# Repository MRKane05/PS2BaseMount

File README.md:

This is a dump of the KiCad project for the Junkstation PS2 project I made a few years ago. I'm really just backing it up for prosperity. 
I'm taking no responsibility for this and it really should be used only as reference.

It's worth noting that there are a couple of mistakes on the board that I haven't fixed:
-The Ethernet wiring for the Mango isn't correct, and troubleshooting it was exceedingly difficult, so much so that I didn't write it down when I got it right, I just put the lid on it
-The Ethernet lines for the Mango shouldn't be pulled down to Ground but pulled to the "R0" pin on the Mango. This allows a successful ethernet connection
-The SD Card slot wired up for game loading through the memory card port is correctly wired

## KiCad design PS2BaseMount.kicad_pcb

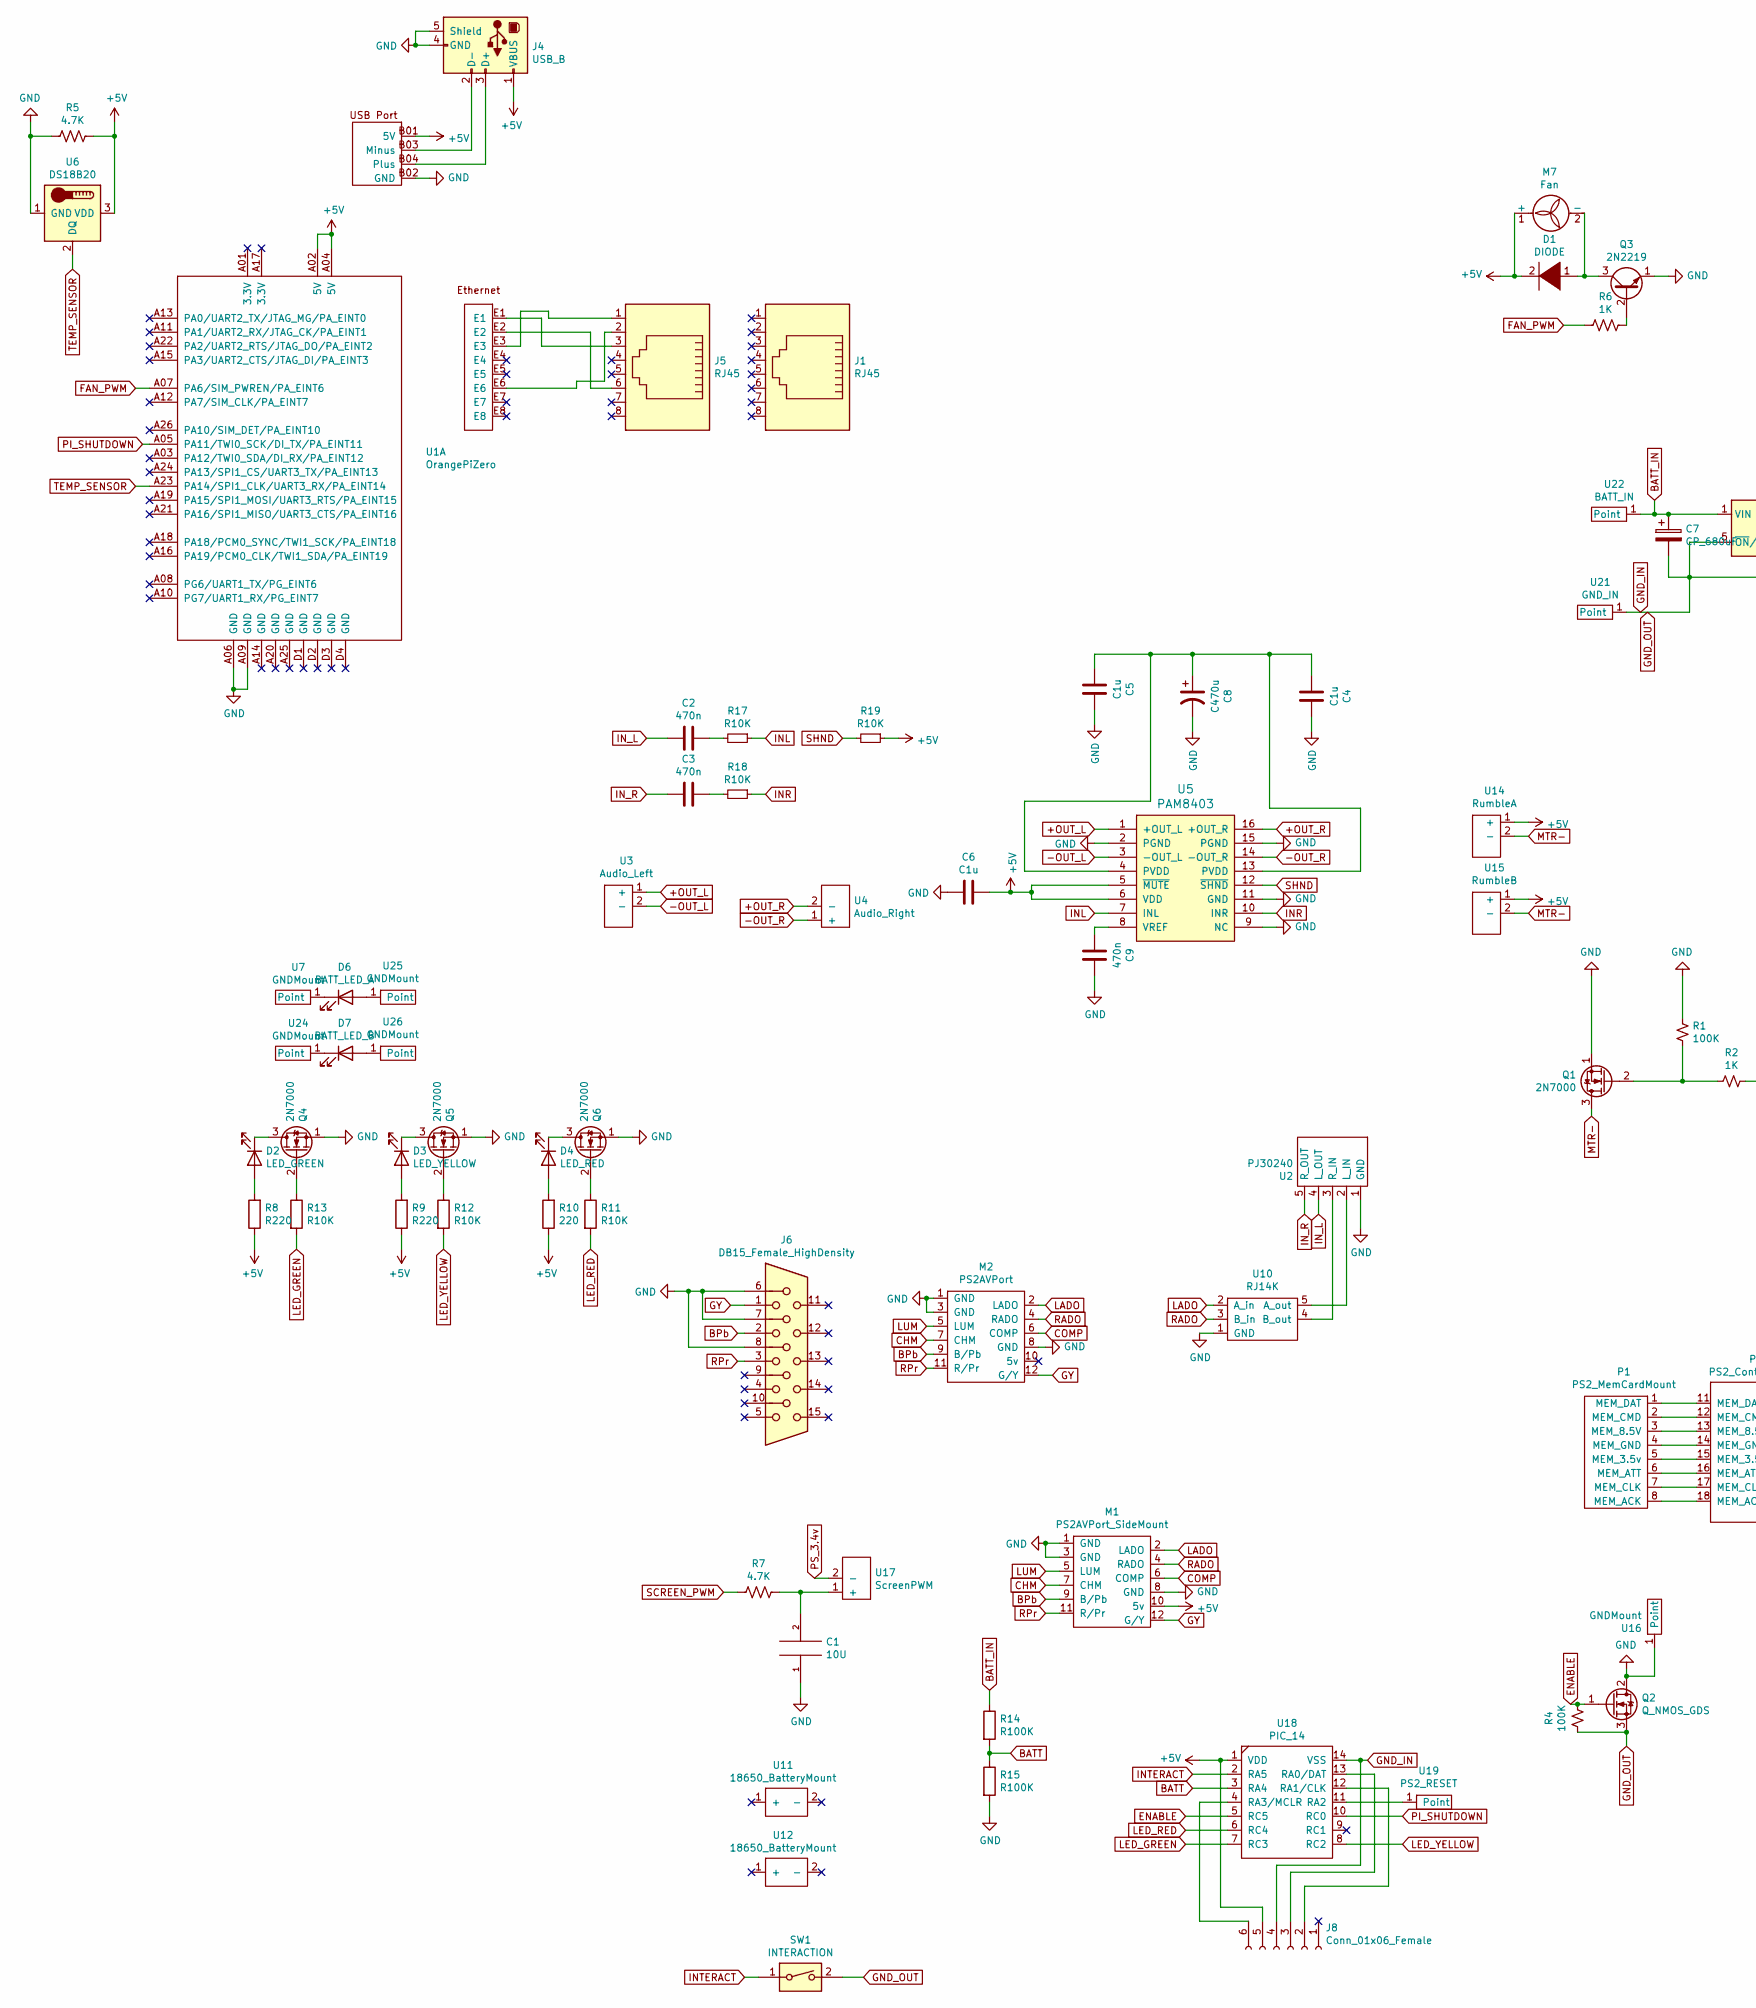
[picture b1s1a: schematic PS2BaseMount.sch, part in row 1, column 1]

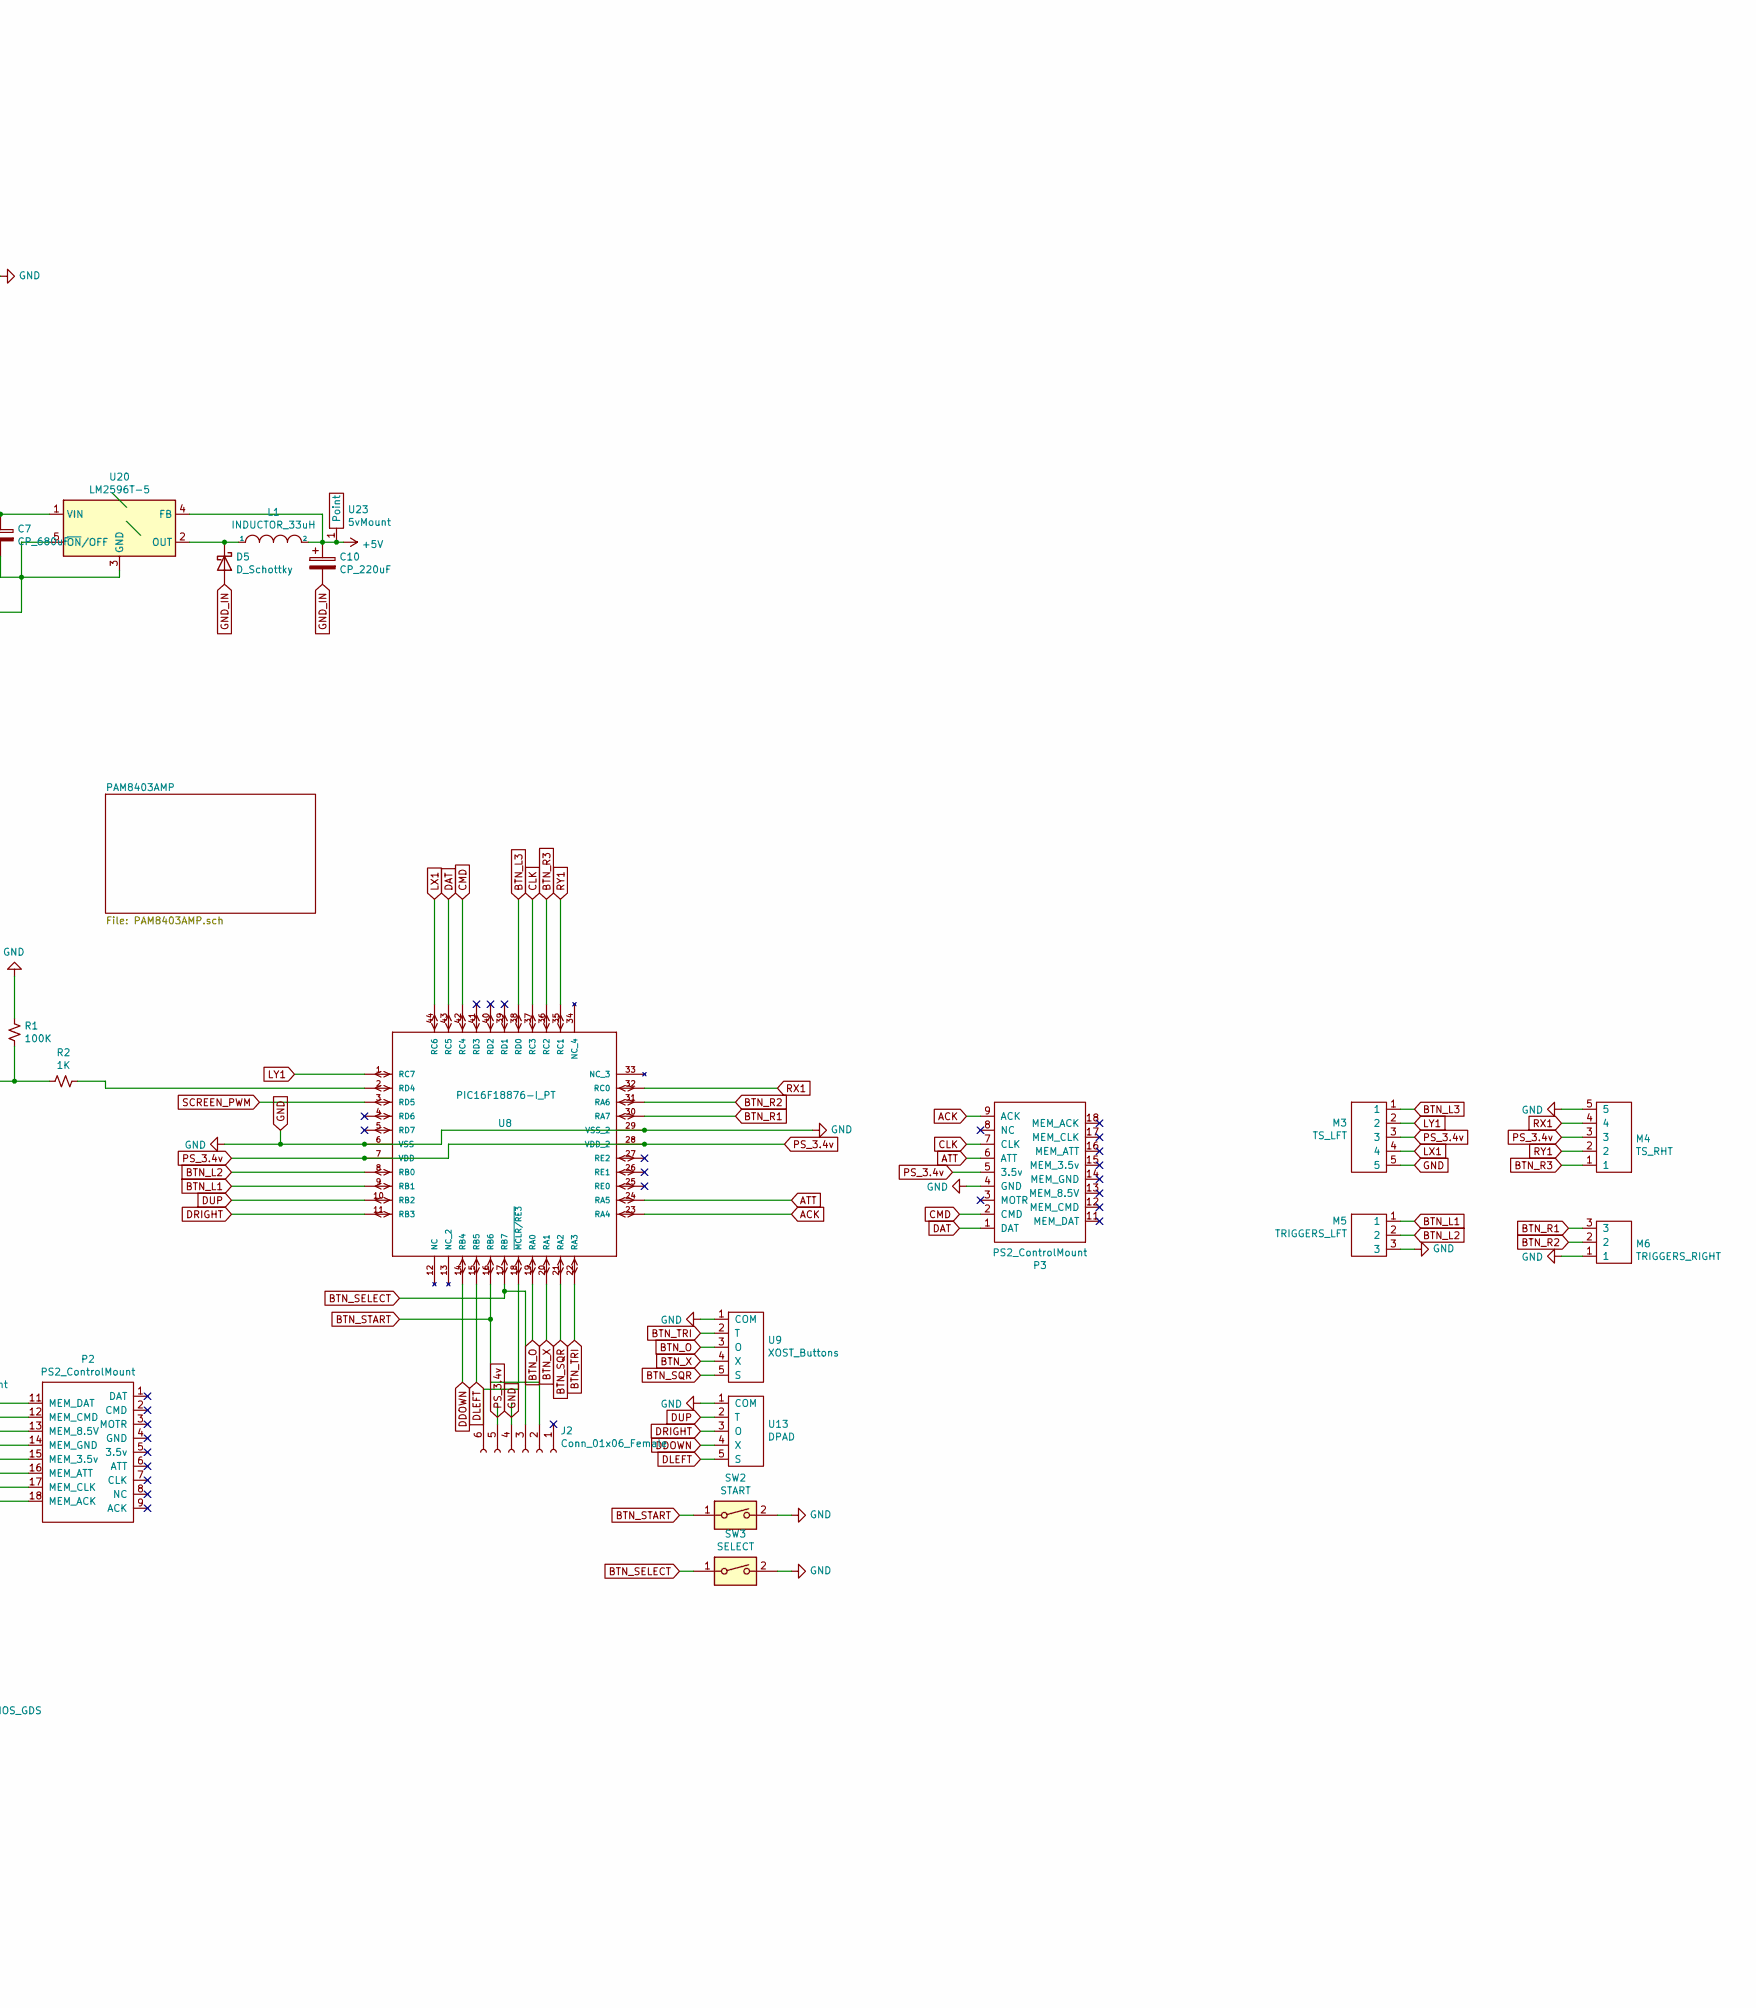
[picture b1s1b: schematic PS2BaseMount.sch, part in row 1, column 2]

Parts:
C1: 10U; C_1206_3216Metric_Pad1.42x1.75mm_HandSolder
C2, C3, C9: 470n; C_1206_3216Metric_Pad1.42x1.75mm_HandSolder; LCSC C1871
C4, C5, C6: C1u; C_1206_3216Metric_Pad1.42x1.75mm_HandSolder; LCSC C1848
C7: CP_680uF; CP_Radial_D8.0mm_P2.50mm
C8: C470u; CP_Radial_D8.0mm_P2.50mm
C10: CP_220uF; CP_Radial_D8.0mm_P3.50mm
D1: DIODE; Crystal_SMD_5032-2Pin_5.0x3.2mm_HandSoldering
D2: LED_GREEN; LED_D3.0mm
D3: LED_YELLOW; LED_D3.0mm
D4: LED_RED; LED_D3.0mm
D5: D_Schottky; Crystal_SMD_5032-2Pin_5.0x3.2mm_HandSoldering; LCSC C8678
D6: BATT_LED_A; LED_D3.0mm
D7: BATT_LED_B; LED_D3.0mm
J1, J5: RJ45; RJ45_Floating
J2, J8: Conn_01x06_Female; PinHeader_1x06_P2.54mm_Horizontal
J4: USB_B; USB_A_Custom_Throughhole_MountGuide
J6: DB15_Female_HighDensity; ScreenBoardArea
L1: INDUCTOR_33uH; L_12x12mm_H8mm; LCSC C169375
M1: PS2AVPort_SideMount; PS2_AVPort_Complete_MountSilk
M2: PS2AVPort; PS2_AVPort_Complete
M3: TS_LFT; JST_1.25_5Pin
M4: TS_RHT; JST_1.25_5Pin
M5: TRIGGERS_LFT; JST_1.25_3Pin
M6: TRIGGERS_RIGHT; JST_1.25_3Pin
M7: Fan; JST_1.5_2Pin
P1: PS2_MemCardMount; PS2_MemCardMountPoints
P2, P3: PS2_ControlMount; PS2_BoardMountFootprint
Q1, Q4, Q5, Q6: 2N7000; 2N7000_HandSolder
Q2: Q_NMOS_GDS; TO-220F-3_Vertical
Q3: 2N2219; 2N7000_HandSolder
R1, R4: 100K; R_1206_3216Metric_Pad1.42x1.75mm_HandSolder
R2, R6: 1K; R_1206_3216Metric_Pad1.42x1.75mm_HandSolder
R5: 4.7K; R_2010_5025Metric_Pad1.52x2.65mm_HandSolder
R7: 4.7K; D_2010_5025Metric_Pad1.52x2.65mm_HandSolder
R8, R9: R220; R_1206_3216Metric_Pad1.42x1.75mm_HandSolder
R10: 220; R_1206_3216Metric_Pad1.42x1.75mm_HandSolder
R11, R12, R13: R10K; R_1206_3216Metric_Pad1.42x1.75mm_HandSolder
R14, R15: R100K; R_1206_3216Metric_Pad1.42x1.75mm_HandSolder
R17, R18, R19: R10K; R_1206_3216Metric_Pad1.42x1.75mm_HandSolder; LCSC C17902
SW1: INTERACTION; SMT_2X4X3.5MM
SW2: START; SquishyTact
SW3: SELECT; SquishyTact
U1: OrangePiZero
U2: PJ30240; AudioJack_PJ30240
U3: Audio_Left; JST_1.5_2Pin
U4: Audio_Right; JST_1.5_2Pin
U5: PAM8403; so-16; LCSC C348830
U6: DS18B20; TO-92_Inline
U7, U16, U24, U25, U26: GNDMount; GND
U8: PIC16F18876-I_PT
U9: XOST_Buttons; XOST_ButtonsV2
U10: RJ14K; RJ14K_Modified
U11, U12: 18650_BatteryMount; 18650_3xHolderV3
U13: DPAD; DPad_Buttons
U14: RumbleA; JST_1.5_2Pin
U15: RumbleB; JST_1.5_2Pin
U17: ScreenPWM; JST_1.5_2Pin
U18: PIC_14; DIP-14_W7.62mm_LongPads
U19: PS2_RESET; GND
U20: LM2596T-5; TO-263-5_TabPin3; LCSC C10002
U21: GND_IN; MountPoint
U22: BATT_IN; MountPoint
U23: 5vMount; MountPoint

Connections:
+5V: C6.1, C10.1, D1.2 (A), J4.1 (VBUS), J8.5, L1.2, M1.10 (5v), M7.1 (+), R5.1, R8.1, R9.1, R10.1, R19.1, U1.A02 (5V), U1.A04 (5V), U1.B01 (5V), U5.5 (~MUTE), U5.6 (VDD), U6.3 (VDD), U14.1 (+), U15.1 (+), U18.1 (VDD), U20.4 (FB), U23.1
+OUT_L: U3.1 (+), U5.1 (+OUT_L)
+OUT_R: U4.2 (-), U5.16 (+OUT_R)
-OUT_L: U3.2 (-), U5.3 (-OUT_L)
-OUT_R: U4.1 (+), U5.14 (-OUT_R)
ACK: P3.9 (ACK), U8.23 (RA4)
ATT: P3.6 (ATT), U8.24 (RA5)
BATT: R14.2, R15.1, U18.3 (RA4)
BATT_IN: C7.1, R14.1, U20.1 (VIN), U22.1
BPb: J6.2, M1.9 (B/Pb), M2.9 (B/Pb)
BTN_L1: M5.1, U8.9 (RB1)
BTN_L2: M5.2, U8.8 (RB0)
BTN_L3: M3.1, U8.38 (RD0)
BTN_O: U8.19 (RA0), U9.3 (O)
BTN_R1: M6.3, U8.30 (RA7)
BTN_R2: M6.2, U8.31 (RA6)
BTN_R3: M4.1, U8.36 (RC2)
BTN_SELECT: J2.3, SW3.1, U8.17 (RB7)
BTN_SQR: U8.21 (RA2), U9.5 (S)
BTN_START: J2.2, SW2.1, U8.16 (RB6)
BTN_TRI: U8.22 (RA3), U9.2 (T)
BTN_X: U8.20 (RA1), U9.4 (X)
CHM: M1.7 (CHM), M2.7 (CHM)
CLK: P3.7 (CLK), U8.37 (RC3)
CMD: P3.2 (CMD), U8.42 (RC4)
COMP: M1.6 (COMP), M2.6 (COMP)
DAT: P3.1 (DAT), U8.43 (RC5)
DDOWN: U8.14 (RB4), U13.4 (X)
DLEFT: U8.15 (RB5), U13.5 (S)
DRIGHT: U8.11 (RB3), U13.3 (O)
DUP: U8.10 (RB2), U13.2 (T)
ENABLE: Q2.1 (G), R4.1, U18.5 (RC5)
FAN_PWM: R6.2, U1.A07 (PA6/SIM_PWREN/PA_EINT6)
GND: C1.1, C4.1, C5.1, C6.2, C8.2, C9.1, J2.4, J4.4 (GND), J4.5 (Shield), J6.6, J6.7, J6.8, M1.1 (GND), M1.3 (GND), M1.8 (GND), M2.1 (GND), M2.3 (GND), M2.8 (GND), M3.5, M4.5, M5.3, M6.1, P3.4 (GND), Q1.1 (S), Q2.2 (D), Q3.1 (E), Q4.1 (S), Q5.1 (S), Q6.1 (S), R1.1, R5.2, R15.2, SW2.2, SW3.2, U1.A06 (GND), U1.A09 (GND), U1.B02 (GND), U2.1 (GND), U5.2 (PGND), U5.9 (NC), U5.11 (GND), U5.15 (PGND), U6.1 (GND), U8.6 (VSS), U8.29 (VSS_2), U9.1 (COM), U10.1 (GND), U13.1 (COM), U16.1
GND_IN: C7.2, C10.2, D5.2 (A), J8.4, Q2.3 (S), R4.2, SW1.2, U18.14 (VSS), U20.3 (GND), U20.5 (~ON~/OFF), U21.1
GY: J6.1, M1.12 (G/Y), M2.12 (G/Y)
INL: R17.1, U5.7 (INL)
INR: R18.1, U5.10 (INR)
INTERACT: SW1.1, U18.2 (RA5)
IN_L: C2.2, U2.4 (L_OUT)
IN_R: C3.2, U2.5 (R_OUT)
LADO: M1.2 (LADO), M2.2 (LADO), U10.2 (A_in)
LED_GREEN: R13.2, U18.7 (RC3)
LED_RED: R11.2, U18.6 (RC4)
LED_YELLOW: R12.2, U18.8 (RC2)
LUM: M1.5 (LUM), M2.5 (LUM)
LX1: M3.4, U8.44 (RC6)
LY1: M3.2, U8.1 (RC7)
MTR-: Q1.3 (D), U14.2 (-), U15.2 (-)
unnamed: C1.2, R7.1, U17.1 (+)
unnamed: C2.1, R17.2
unnamed: C3.1, R18.2
unnamed: C4.2, C5.2, C8.1, U5.4 (PVDD), U5.13 (PVDD)
unnamed: C9.2, U5.8 (VREF)
unnamed: D1.1 (K), M7.2 (-), Q3.3 (C)
unnamed: D2.1 (K), Q4.3 (D)
unnamed: D2.2 (A), R8.2
unnamed: D3.1 (K), Q5.3 (D)
unnamed: D3.2 (A), R9.2
unnamed: D4.1 (K), Q6.3 (D)
unnamed: D4.2 (A), R10.2
unnamed: D5.1 (K), L1.1, U20.2 (OUT)
unnamed: D6.1 (K), U7.1
unnamed: D6.2 (A), U25.1
unnamed: D7.1 (K), U24.1
unnamed: D7.2 (A), U26.1
unnamed: J2.6, U8.18 (~MCLR/RE3)
unnamed: J4.2 (D-), U1.B03 (Minus)
unnamed: J4.3 (D+), U1.B04 (Plus)
unnamed: J5.1, U1.E3
unnamed: J5.2, U1.E6
unnamed: J5.3, U1.E1
unnamed: J5.6, U1.E2
unnamed: J8.2, U18.12 (RA1/CLK)
unnamed: J8.3, U18.13 (RA0/DAT)
unnamed: J8.6, U18.4 (RA3/MCLR)
unnamed: P1.1 (MEM_DAT), P2.11 (MEM_DAT)
unnamed: P1.2 (MEM_CMD), P2.12 (MEM_CMD)
unnamed: P1.3 (MEM_8.5V), P2.13 (MEM_8.5V)
unnamed: P1.4 (MEM_GND), P2.14 (MEM_GND)
unnamed: P1.5 (MEM_3.5v), P2.15 (MEM_3.5v)
unnamed: P1.6 (MEM_ATT), P2.16 (MEM_ATT)
unnamed: P1.7 (MEM_CLK), P2.17 (MEM_CLK)
unnamed: P1.8 (MEM_ACK), P2.18 (MEM_ACK)
unnamed: Q1.2 (G), R1.2, R2.2
unnamed: Q3.2 (B), R6.1
unnamed: Q4.2 (G), R13.1
unnamed: Q5.2 (G), R12.1
unnamed: Q6.2 (G), R11.1
unnamed: R2.1, U8.2 (RD4)
unnamed: U2.3 (R_IN), U10.4 (B_out)
unnamed: U2.2 (L_IN), U10.5 (A_out)
unnamed: U18.11 (RA2), U19.1
PI_SHUTDOWN: U1.A05 (PA11/TWI0_SCK/DI_TX/PA_EINT11), U18.10 (RC0)
PS_3.4v: J2.5, M3.3, M4.3, P3.5 (3.5v), U8.7 (VDD), U8.28 (VDD_2), U17.2 (-)
RADO: M1.4 (RADO), M2.4 (RADO), U10.3 (B_in)
RPr: J6.3, M1.11 (R/Pr), M2.11 (R/Pr)
RX1: M4.4, U8.32 (RC0)
RY1: M4.2, U8.35 (RC1)
SCREEN_PWM: R7.2, U8.3 (RD5)
SHND: R19.2, U5.12 (~SHND)
TEMP_SENSOR: U1.A23 (PA14/SPI1_CLK/UART3_RX/PA_EINT14), U6.2 (DQ)

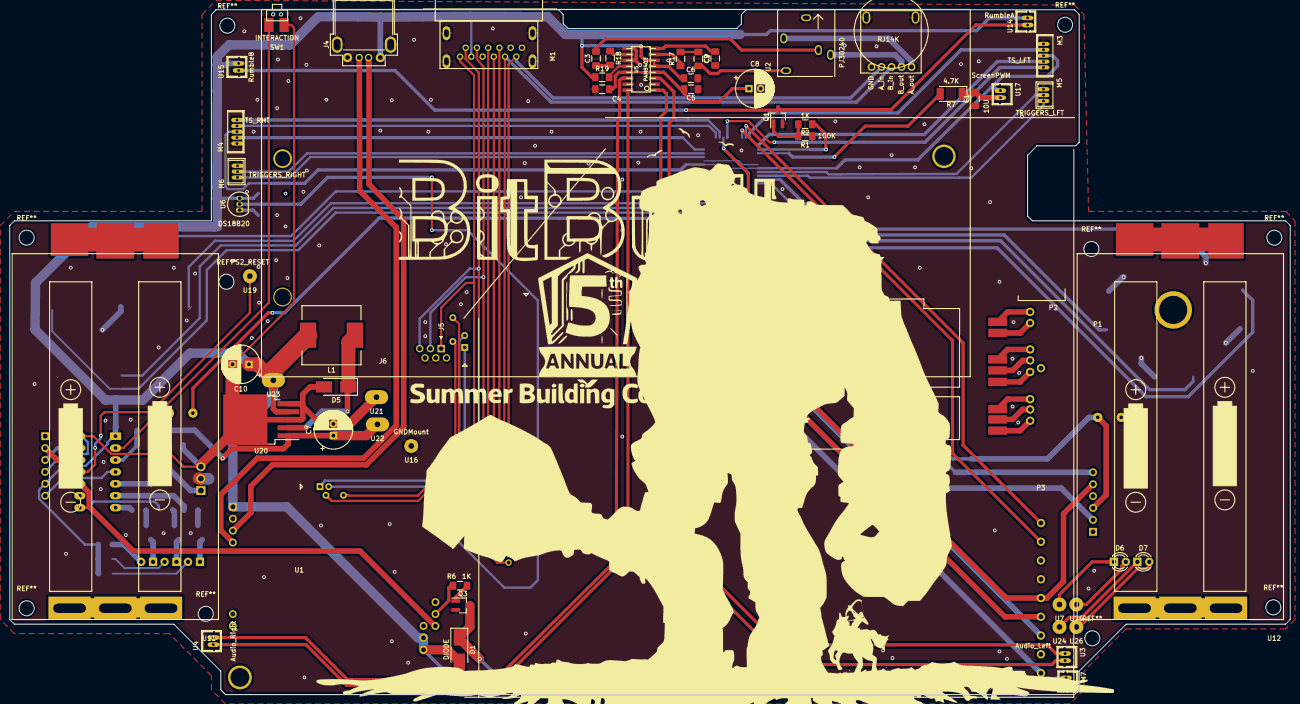
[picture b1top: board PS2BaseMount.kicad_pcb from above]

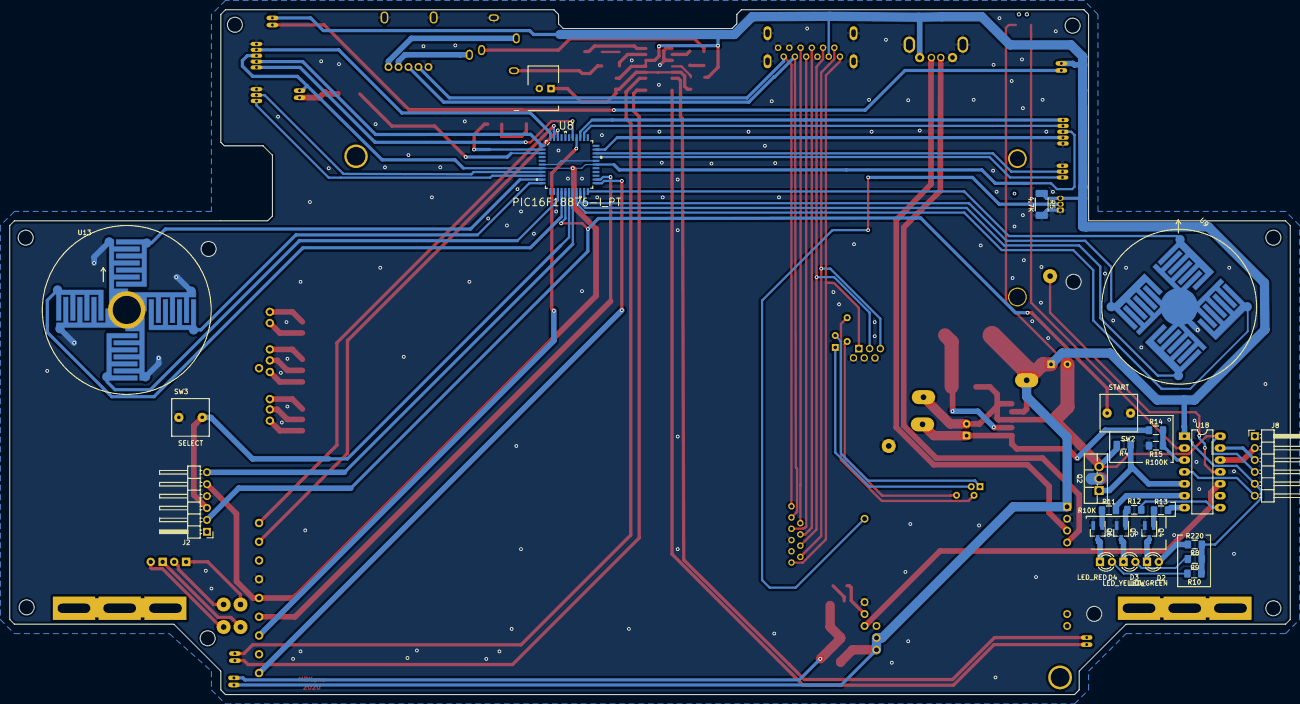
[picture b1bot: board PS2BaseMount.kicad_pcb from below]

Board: 2 copper layers, 273.0 x 146.0 mm, 86 parts (25 on the bottom side), 102 nets.

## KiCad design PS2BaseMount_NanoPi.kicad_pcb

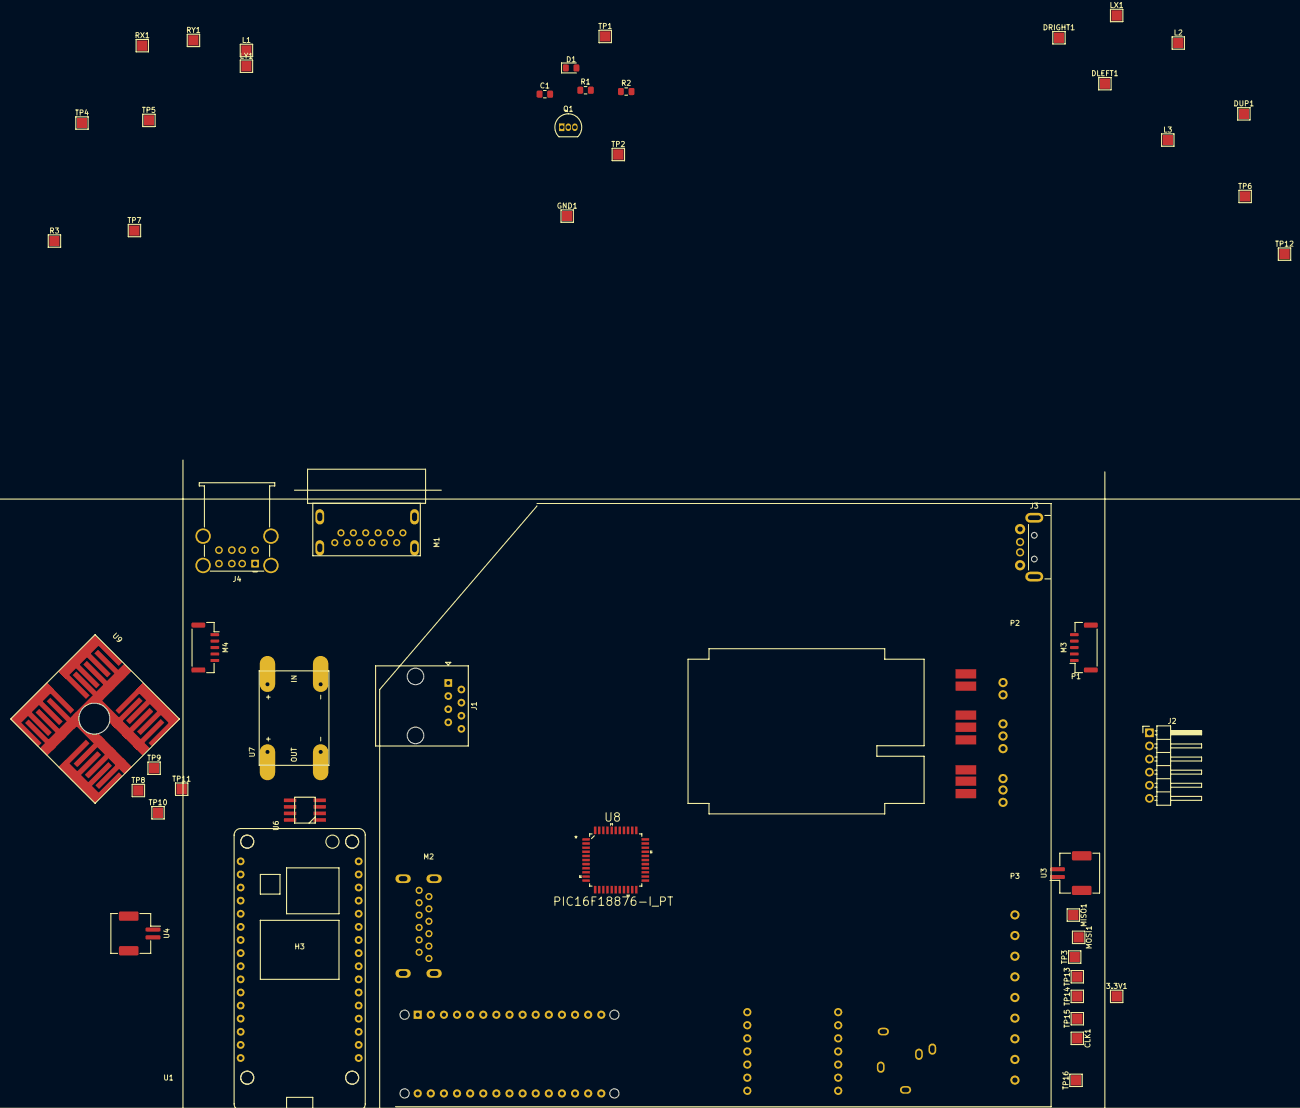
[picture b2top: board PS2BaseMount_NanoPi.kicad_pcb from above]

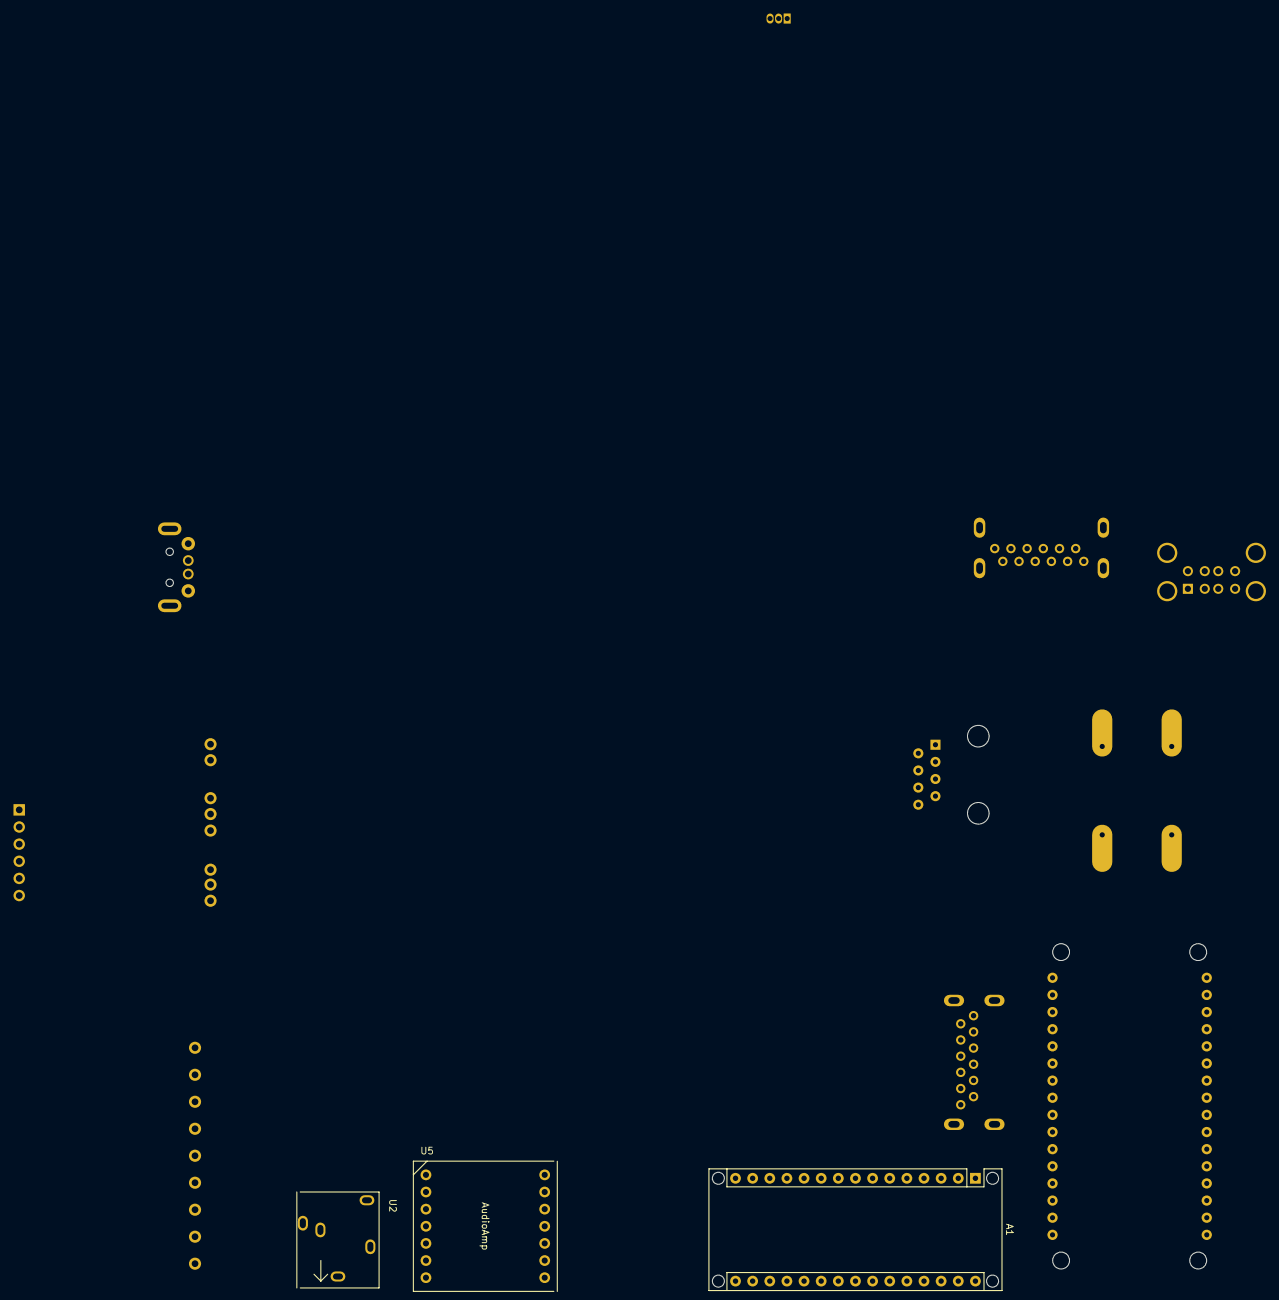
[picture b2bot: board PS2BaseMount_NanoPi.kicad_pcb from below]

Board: 2 copper layers, 58 parts (3 on the bottom side), 46 nets, no tracks yet.

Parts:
3.3V1: TP6; TestPoint_Pad_2.0x2.0mm
A1: Arduino_Nano_v3.x; Arduino_Nano_WithMountingHoles
C1: 10uF; C_0805_2012Metric_Pad1.15x1.40mm_HandSolder
CLK1: TP19; TestPoint_Pad_2.0x2.0mm
D1: 1N58XX; D_0805_2012Metric_Pad1.15x1.40mm_HandSolder
DLEFT1: TP7; TestPoint_Pad_2.0x2.0mm
DRIGHT1: TP8; TestPoint_Pad_2.0x2.0mm
DUP1: TP27; TestPoint_Pad_2.0x2.0mm
GND1: TP5; TestPoint_Pad_2.0x2.0mm
J1: RJ45; RJ45_Amphenol_54602-x08_Horizontal
J2: Conn_01x06_Female; PinHeader_1x06_P2.54mm_Horizontal
J3: USB_B; USB_A_Custom_Throughhole
J4: USB_A_Dual; USB_A_Wuerth_61400826021_Horizontal_Stacked
L1: TP9; TestPoint_Pad_2.0x2.0mm
L2: TP10; TestPoint_Pad_2.0x2.0mm
L3: TP20; TestPoint_Pad_2.0x2.0mm
LX1: TP26; TestPoint_Pad_2.0x2.0mm
LY1: TP23; TestPoint_Pad_2.0x2.0mm
M1: PS2AVPort_SideMount; PS2_AVPort_Complete_MountSilk
M2: PS2AVPort; PS2_AVPort_Complete
M3: TS_LFT; JST_GH_SM05B-GHS-TB_1x05-1MP_P1.25mm_Horizontal
M4: TS_RHT; JST_GH_SM05B-GHS-TB_1x05-1MP_P1.25mm_Horizontal
MISO1: TP12; TestPoint_Pad_2.0x2.0mm
MOSI1: TP13; TestPoint_Pad_2.0x2.0mm
P1: PS2_MemCardMount; PS2_MemCardMountPoints
P2, P3: PS2_ControlMount; PS2_BoardMountFootprint
Q1: 2N7000; TO-92_Inline
R1: 100K; R_0805_2012Metric_Pad1.15x1.40mm_HandSolder
R2: 1K; R_0805_2012Metric_Pad1.15x1.40mm_HandSolder
R3: TP18; TestPoint_Pad_2.0x2.0mm
RX1: TP11; TestPoint_Pad_2.0x2.0mm
RY1: TP4; TestPoint_Pad_2.0x2.0mm
TP1: MTR-; TestPoint_Pad_2.0x2.0mm
TP2: MTR+; TestPoint_Pad_2.0x2.0mm
TP3: 8.5V; TestPoint_Pad_2.0x2.0mm
TP4: R1; TestPoint_Pad_2.0x2.0mm
TP5: R2; TestPoint_Pad_2.0x2.0mm
TP6: SL; TestPoint_Pad_2.0x2.0mm
TP7: ST; TestPoint_Pad_2.0x2.0mm
TP8: SQ; TestPoint_Pad_2.0x2.0mm
TP9: TRI; TestPoint_Pad_2.0x2.0mm
TP10: X; TestPoint_Pad_2.0x2.0mm
TP11: CIR; TestPoint_Pad_2.0x2.0mm
TP12: DDOWN; TestPoint_Pad_2.0x2.0mm
TP13: GND; TestPoint_Pad_2.0x2.0mm
TP14: 3.3V; TestPoint_Pad_2.0x2.0mm
TP15: CS; TestPoint_Pad_2.0x2.0mm
TP16: ACK; TestPoint_Pad_2.0x2.0mm
U1: NanoPiDUO2; NanoPIDUO2
U2: PJ30240; AudioJack_PJ30240
U3: Audio_Left; JST_ZE_SM02B-ZESS-TBT_1x02-1MP_P1.50mm_Horizontal
U4: Audio_Right; JST_ZE_SM02B-ZESS-TBT_1x02-1MP_P1.50mm_Horizontal
U5: AudioAmp; PAM8803_AudioAmp
U6: DMosfet_AO9926B; DualMosfet AO9926B
U7: 5VBuckBoost; PS2BuckBoost
U8: PIC16F18876-I_PT
U9: XOST_Buttons

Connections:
GND: GND1.1, J2.4, P3.4, Q1.1, R1.1, TP13.1, U2.1, U3.MP, U4.MP, U8.6, U8.29
unnamed: C1.1, D1.2, Q1.3, TP1.1
unnamed: C1.2, D1.1, P3.3, TP2.1, TP3.1
unnamed: CLK1.1, P3.7, U8.37
unnamed: DLEFT1.1, U8.8
unnamed: DRIGHT1.1, U8.9
unnamed: DUP1.1, U8.31
unnamed: J2.2, TP6.1, U8.16
unnamed: J2.3, TP7.1, U8.17
unnamed: J2.6, U8.18
unnamed: L1.1, U8.10
unnamed: L2.1, U8.11
unnamed: L3.1, U8.36
unnamed: LX1.1, U8.32
unnamed: LY1.1, U8.35
unnamed: M2.2, U5.8
unnamed: M2.4, U5.10
unnamed: MISO1.1, P3.1, U8.43
unnamed: MOSI1.1, P3.2, U8.42
unnamed: P1.1, P2.11
unnamed: P1.2, P2.12
unnamed: P1.3, P2.13
unnamed: P1.4, P2.14
unnamed: P1.5, P2.15
unnamed: P1.6, P2.16
unnamed: P1.7, P2.17
unnamed: P1.8, P2.18
unnamed: P3.6, TP15.1, U8.24
unnamed: P3.9, TP16.1, U8.23
unnamed: Q1.2, R1.2, R2.2
unnamed: R2.1, U8.2
unnamed: R3.1, U8.38
unnamed: RX1.1, U8.44
unnamed: RY1.1, U8.1
unnamed: TP4.1, U8.14
unnamed: TP5.1, U8.15
unnamed: TP8.1, U8.19, U9.5
unnamed: TP9.1, U8.20, U9.2
unnamed: TP10.1, U8.21, U9.4
unnamed: TP11.1, U8.22, U9.3
unnamed: TP12.1, U8.30
unnamed: U2.2, U3.1, U5.5
unnamed: U2.3, U4.1, U5.7
unnamed: U3.2, U5.4
unnamed: U4.2, U5.6
Vdd: 3.3V1.1, J2.5, P3.5, TP14.1, U8.7, U8.28

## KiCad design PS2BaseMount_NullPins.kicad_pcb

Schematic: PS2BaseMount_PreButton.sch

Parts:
A1: Arduino_Nano_v3.x; Arduino_Nano_WithMountingHoles
J1: USB_B; USB_A_Custom_Throughhole
J2: USB_A_Dual; USB_A_Wuerth_61400826021_Horizontal_Stacked
J3: RJ45; RJ45_Amphenol_54602-x08_Horizontal
M1: PS2AVPort; PS2_AVPort_Complete
M2: TS_LFT; JST_GH_SM05B-GHS-TB_1x05-1MP_P1.25mm_Horizontal
M3: TS_RHT; JST_GH_SM05B-GHS-TB_1x05-1MP_P1.25mm_Horizontal
M4: Fan; 2Point_Mount
M5: PS2AVPort_SideMount; PS2_AVPort_Complete_MountSilk
P1, P2: PS2_ControlMount; PS2_BoardMountFootprint
P3: PS2_MemCardMount; PS2_MemCardMountPoints
Q1: MJE3305; TO-126-3_Vertical
R1: 4.7K; R_2010_5025Metric_Pad1.52x2.65mm_HandSolder
R2: 1K; R_2512_6332Metric_Pad1.52x3.35mm_HandSolder
R3: Fan_J+; SolderJumper-2_P1.3mm_Open_RoundedPad1.0x1.5mm
R4: Fan_J-; SolderJumper-2_P1.3mm_Open_RoundedPad1.0x1.5mm
RV1: R_POT_US; Potentiometer_Triwood_RM-065
TH1: Thermistor_PTC; 2Point_Mount
U1: AudioAmp; PAM8803_AudioAmp
U2: LM358; LM358(SMD)
U3: PJ30240; AudioJack_PJ30240
U4: Audio_Left; JST_ZE_SM02B-ZESS-TBT_1x02-1MP_P1.50mm_Horizontal
U5: Audio_Right; JST_ZE_SM02B-ZESS-TBT_1x02-1MP_P1.50mm_Horizontal
m1: 10P_LFT; Hirose_FH12-10S-0.5SH_1x10-1MP_P0.50mm_Horizontal
m2: 10P_RHT; Hirose_FH12-10S-0.5SH_1x10-1MP_P0.50mm_Horizontal

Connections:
+5V: R1.1, R3.1, RV1.1, U2.8
GND: R4.1, RV1.3, TH1.2, U2.4, U3.1, U4.MP, U5.MP
unnamed: M1.2, U1.8
unnamed: M1.4, U1.10
unnamed: M4.1 (+), Q1.3
unnamed: M4.2 (-), R4.2
unnamed: Q1.1, R2.1
unnamed: Q1.2, R3.2
unnamed: R1.2, TH1.1, U2.2
unnamed: R2.2, U2.1
unnamed: RV1.2, U2.3
unnamed: U1.4, U4.2
unnamed: U1.5, U3.2, U4.1
unnamed: U1.6, U5.2
unnamed: U1.7, U3.3, U5.1

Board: 2 copper layers, 24 parts (1 on the bottom side), 15 nets, no tracks yet.

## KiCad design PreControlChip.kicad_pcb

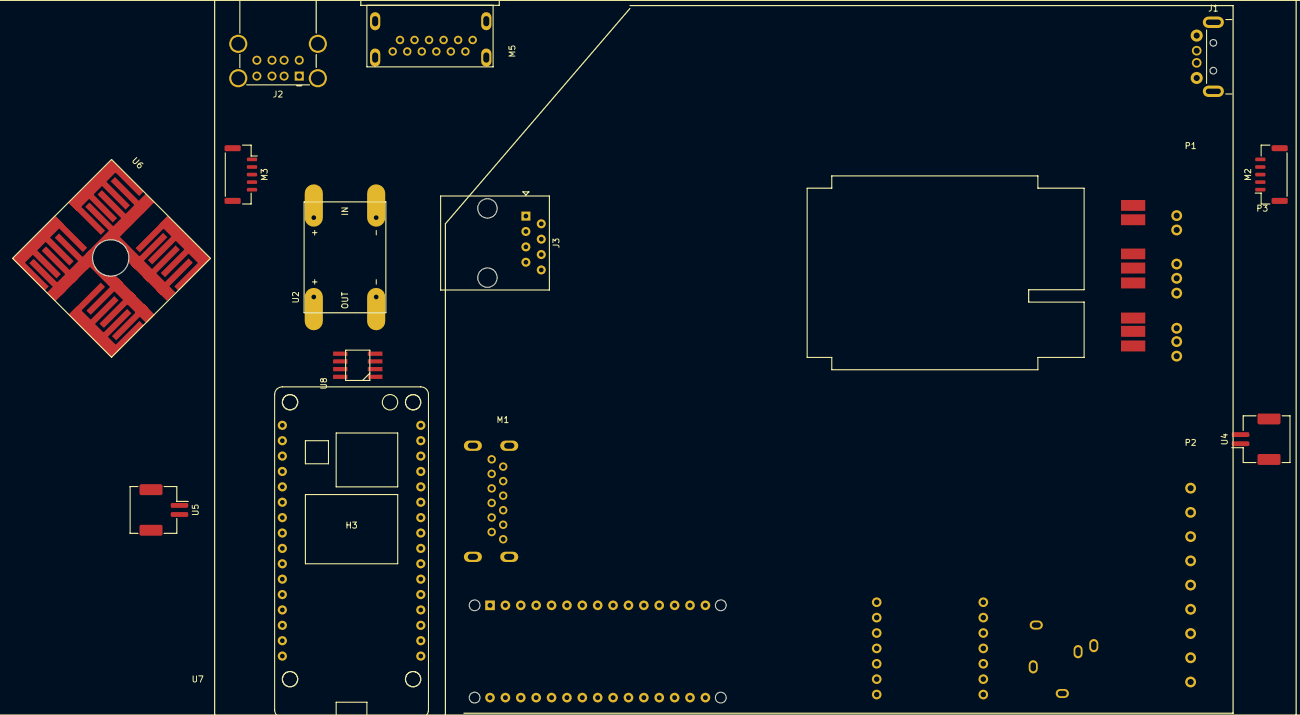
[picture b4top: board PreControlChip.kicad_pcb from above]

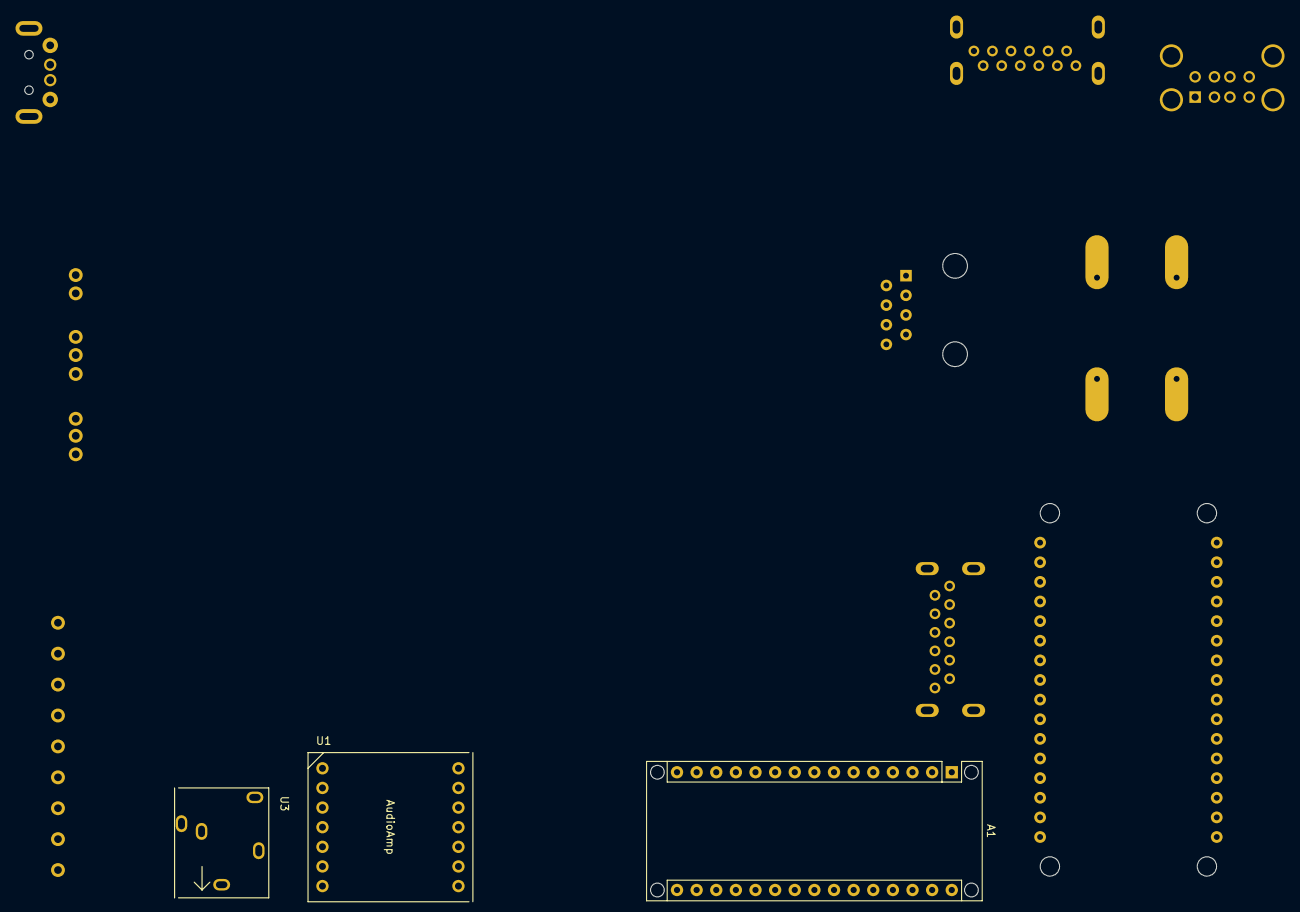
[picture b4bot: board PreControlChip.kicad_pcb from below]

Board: 2 copper layers, 19 parts (3 on the bottom side), 15 nets, no tracks yet.

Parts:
A1: Arduino_Nano_v3.x; Arduino_Nano_WithMountingHoles
J1: USB_B; USB_A_Custom_Throughhole
J2: USB_A_Dual; USB_A_Wuerth_61400826021_Horizontal_Stacked
J3: RJ45; RJ45_Amphenol_54602-x08_Horizontal
M1: PS2AVPort; PS2_AVPort_Complete
M2: TS_LFT; JST_GH_SM05B-GHS-TB_1x05-1MP_P1.25mm_Horizontal
M3: TS_RHT; JST_GH_SM05B-GHS-TB_1x05-1MP_P1.25mm_Horizontal
M5: PS2AVPort_SideMount; PS2_AVPort_Complete_MountSilk
P1, P2: PS2_ControlMount; PS2_BoardMountFootprint
P3: PS2_MemCardMount; PS2_MemCardMountPoints
U1: AudioAmp; PAM8803_AudioAmp
U2: 5VBuckBoost; PS2BuckBoost
U3: PJ30240; AudioJack_PJ30240
U4: Audio_Left; JST_ZE_SM02B-ZESS-TBT_1x02-1MP_P1.50mm_Horizontal
U5: Audio_Right; JST_ZE_SM02B-ZESS-TBT_1x02-1MP_P1.50mm_Horizontal
U6: XOST_Buttons
U7: NanoPiDUO2; NanoPIDUO2
U8: DMosfet_AO9926B; DualMosfet AO9926B

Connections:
GND: U3.1, U4.MP, U5.MP
unnamed: M1.2, U1.8
unnamed: M1.4, U1.10
unnamed: P1.11, P3.1
unnamed: P1.12, P3.2
unnamed: P1.13, P3.3
unnamed: P1.14, P3.4
unnamed: P1.15, P3.5
unnamed: P1.16, P3.6
unnamed: P1.17, P3.7
unnamed: P1.18, P3.8
unnamed: U1.4, U4.2
unnamed: U1.5, U3.2, U4.1
unnamed: U1.6, U5.2
unnamed: U1.7, U3.3, U5.1

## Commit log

2024-12-11 Project dumped onto GIT
